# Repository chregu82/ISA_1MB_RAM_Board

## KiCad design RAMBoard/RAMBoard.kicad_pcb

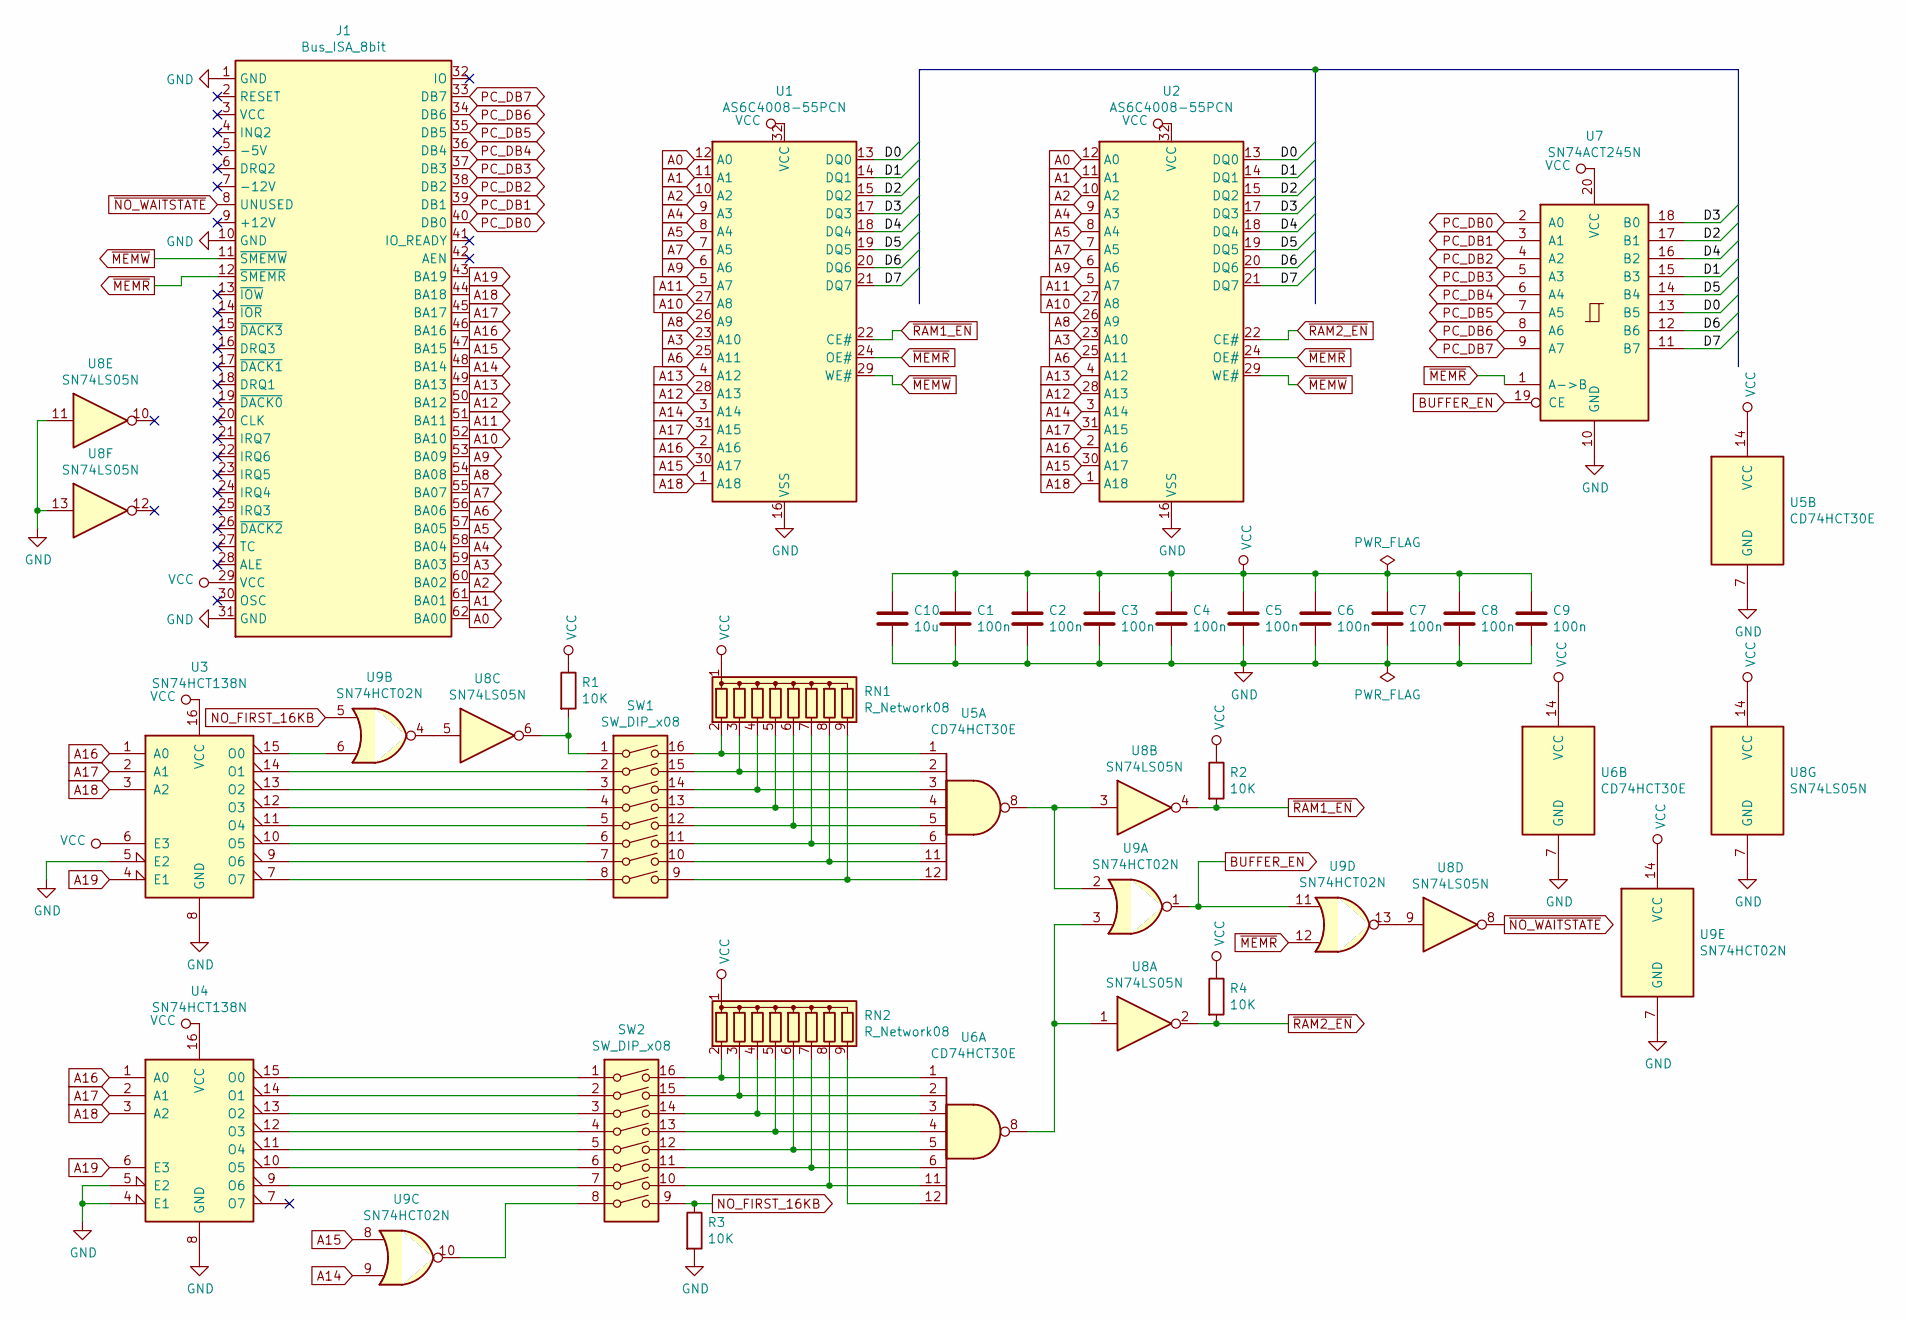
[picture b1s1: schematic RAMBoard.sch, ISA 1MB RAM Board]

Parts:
C1, C2, C3, C4, C5, C6, C7, C8, C9: 100n; C_Disc_D5.0mm_W2.5mm_P2.50mm
C10: 10u; C_Disc_D5.0mm_W2.5mm_P2.50mm
J1: Bus_ISA_8bit; BUS_XT
R1, R2, R3, R4: 10K; R_Axial_DIN0204_L3.6mm_D1.6mm_P5.08mm_Horizontal
RN1, RN2: R_Network08; R_Array_SIP9
SW1, SW2: SW_DIP_x08; SW_DIP_SPSTx08_Slide_9.78x22.5mm_W7.62mm_P2.54mm
U1, U2: AS6C4008-55PCN; DIP-32_W15.24mm
U3, U4: SN74HCT138N; DIP-16_W7.62mm
U5, U6: CD74HCT30E; DIP-14_W7.62mm
U7: SN74ACT245N; DIP-20_W7.62mm
U8: SN74LS05N; DIP-14_W7.62mm
U9: SN74HCT02N; DIP-14_W7.62mm

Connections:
/D0: U1.13 (DQ0), U2.13 (DQ0), U7.13 (B5)
/D1: U1.14 (DQ1), U2.14 (DQ1), U7.15 (B3)
/D2: U1.15 (DQ2), U2.15 (DQ2), U7.17 (B1)
/D3: U1.17 (DQ3), U2.17 (DQ3), U7.18 (B0)
/D4: U1.18 (DQ4), U2.18 (DQ4), U7.16 (B2)
/D5: U1.19 (DQ5), U2.19 (DQ5), U7.14 (B4)
/D6: U1.20 (DQ6), U2.20 (DQ6), U7.12 (B6)
/D7: U1.21 (DQ7), U2.21 (DQ7), U7.11 (B7)
A0: J1.62 (BA00), U1.12 (A0), U2.12 (A0)
A1: J1.61 (BA01), U1.11 (A1), U2.11 (A1)
A2: J1.60 (BA02), U1.10 (A2), U2.10 (A2)
A3: J1.59 (BA03), U1.23 (A10), U2.23 (A10)
A4: J1.58 (BA04), U1.9 (A3), U2.9 (A3)
A5: J1.57 (BA05), U1.8 (A4), U2.8 (A4)
A6: J1.56 (BA06), U1.25 (A11), U2.25 (A11)
A7: J1.55 (BA07), U1.7 (A5), U2.7 (A5)
A8: J1.54 (BA08), U1.26 (A9), U2.26 (A9)
A9: J1.53 (BA09), U1.6 (A6), U2.6 (A6)
A10: J1.52 (BA10), U1.27 (A8), U2.27 (A8)
A11: J1.51 (BA11), U1.5 (A7), U2.5 (A7)
A12: J1.50 (BA12), U1.28 (A13), U2.28 (A13)
A13: J1.49 (BA13), U1.4 (A12), U2.4 (A12)
A14: J1.48 (BA14), U1.3 (A14), U2.3 (A14), U9.9
A15: J1.47 (BA15), U1.30 (A17), U2.30 (A17), U9.8
A16: J1.46 (BA16), U1.2 (A16), U2.2 (A16), U3.1 (A0), U4.1 (A0)
A17: J1.45 (BA17), U1.31 (A15), U2.31 (A15), U3.2 (A1), U4.2 (A1)
A18: J1.44 (BA18), U1.1 (A18), U2.1 (A18), U3.3 (A2), U4.3 (A2)
A19: J1.43 (BA19), U3.4 (E1), U4.6 (E3)
BUFFER_EN: U7.19 (CE), U9.1, U9.11
GND: C1.2, C2.2, C3.2, C4.2, C5.2, C6.2, C7.2, C8.2, C9.2, C10.2, J1.1 (GND), J1.10 (GND), J1.31 (GND), R3.2, U1.16 (VSS), U2.16 (VSS), U3.5 (E2), U3.8 (GND), U4.4 (E1), U4.5 (E2), U4.8 (GND), U5.7 (GND), U6.7 (GND), U7.10 (GND), U8.7 (GND), U8.11, U8.13, U9.7 (GND); also elsewhere on the board
NO_FIRST_16KB: R3.1, SW2.9, U9.5
unnamed: R1.2, SW1.1, U8.6
unnamed: RN1.2 (R1), SW1.16, U5.1
unnamed: RN1.3 (R2), SW1.15, U5.2
unnamed: RN1.4 (R3), SW1.14, U5.3
unnamed: RN1.5 (R4), SW1.13, U5.4
unnamed: RN1.6 (R5), SW1.12, U5.5
unnamed: RN1.7 (R6), SW1.11, U5.6
unnamed: RN1.8 (R7), SW1.10, U5.11
unnamed: RN1.9 (R8), SW1.9, U5.12
unnamed: RN2.2 (R1), SW2.16, U6.1
unnamed: RN2.3 (R2), SW2.15, U6.2
unnamed: RN2.4 (R3), SW2.14, U6.3
unnamed: RN2.5 (R4), SW2.13, U6.4
unnamed: RN2.6 (R5), SW2.12, U6.5
unnamed: RN2.7 (R6), SW2.11, U6.6
unnamed: RN2.8 (R7), SW2.10, U6.11
unnamed: RN2.9 (R8), U6.12
unnamed: SW1.2, U3.14 (O1)
unnamed: SW1.3, U3.13 (O2)
unnamed: SW1.4, U3.12 (O3)
unnamed: SW1.5, U3.11 (O4)
unnamed: SW1.6, U3.10 (O5)
unnamed: SW1.7, U3.9 (O6)
unnamed: SW1.8, U3.7 (O7)
unnamed: SW2.1, U4.15 (O0)
unnamed: SW2.2, U4.14 (O1)
unnamed: SW2.3, U4.13 (O2)
unnamed: SW2.4, U4.12 (O3)
unnamed: SW2.5, U4.11 (O4)
unnamed: SW2.6, U4.10 (O5)
unnamed: SW2.7, U4.9 (O6)
unnamed: SW2.8, U9.10
unnamed: U3.15 (O0), U9.6
unnamed: U5.8, U8.3, U9.2
unnamed: U6.8, U8.1, U9.3
unnamed: U8.5, U9.4
unnamed: U8.9, U9.13
PC_DB0: J1.40 (DB0), U7.2 (A0)
PC_DB1: J1.39 (DB1), U7.3 (A1)
PC_DB2: J1.38 (DB2), U7.4 (A2)
PC_DB3: J1.37 (DB3), U7.5 (A3)
PC_DB4: J1.36 (DB4), U7.6 (A4)
PC_DB5: J1.35 (DB5), U7.7 (A5)
PC_DB6: J1.34 (DB6), U7.8 (A6)
PC_DB7: J1.33 (DB7), U7.9 (A7)
VCC: C1.1, C2.1, C3.1, C4.1, C5.1, C6.1, C7.1, C8.1, C9.1, C10.1, J1.29 (VCC), R1.1, R2.1, R4.1, RN1.1 (common), RN2.1 (common), U1.32 (VCC), U2.32 (VCC), U3.6 (E3), U3.16 (VCC), U4.16 (VCC), U5.14 (VCC), U6.14 (VCC), U7.20 (VCC), U8.14 (VCC), U9.14 (VCC)
~MEMR: J1.12 (~SMEMR), U1.24 (OE#), U2.24 (OE#), U7.1 (A->B), U9.12
~MEMW: J1.11 (~SMEMW), U1.29 (WE#), U2.29 (WE#)
~NO_WAITSTATE: J1.8 (UNUSED), U8.8
~RAM1_EN: R2.2, U1.22 (CE#), U8.4
~RAM2_EN: R4.2, U2.22 (CE#), U8.2

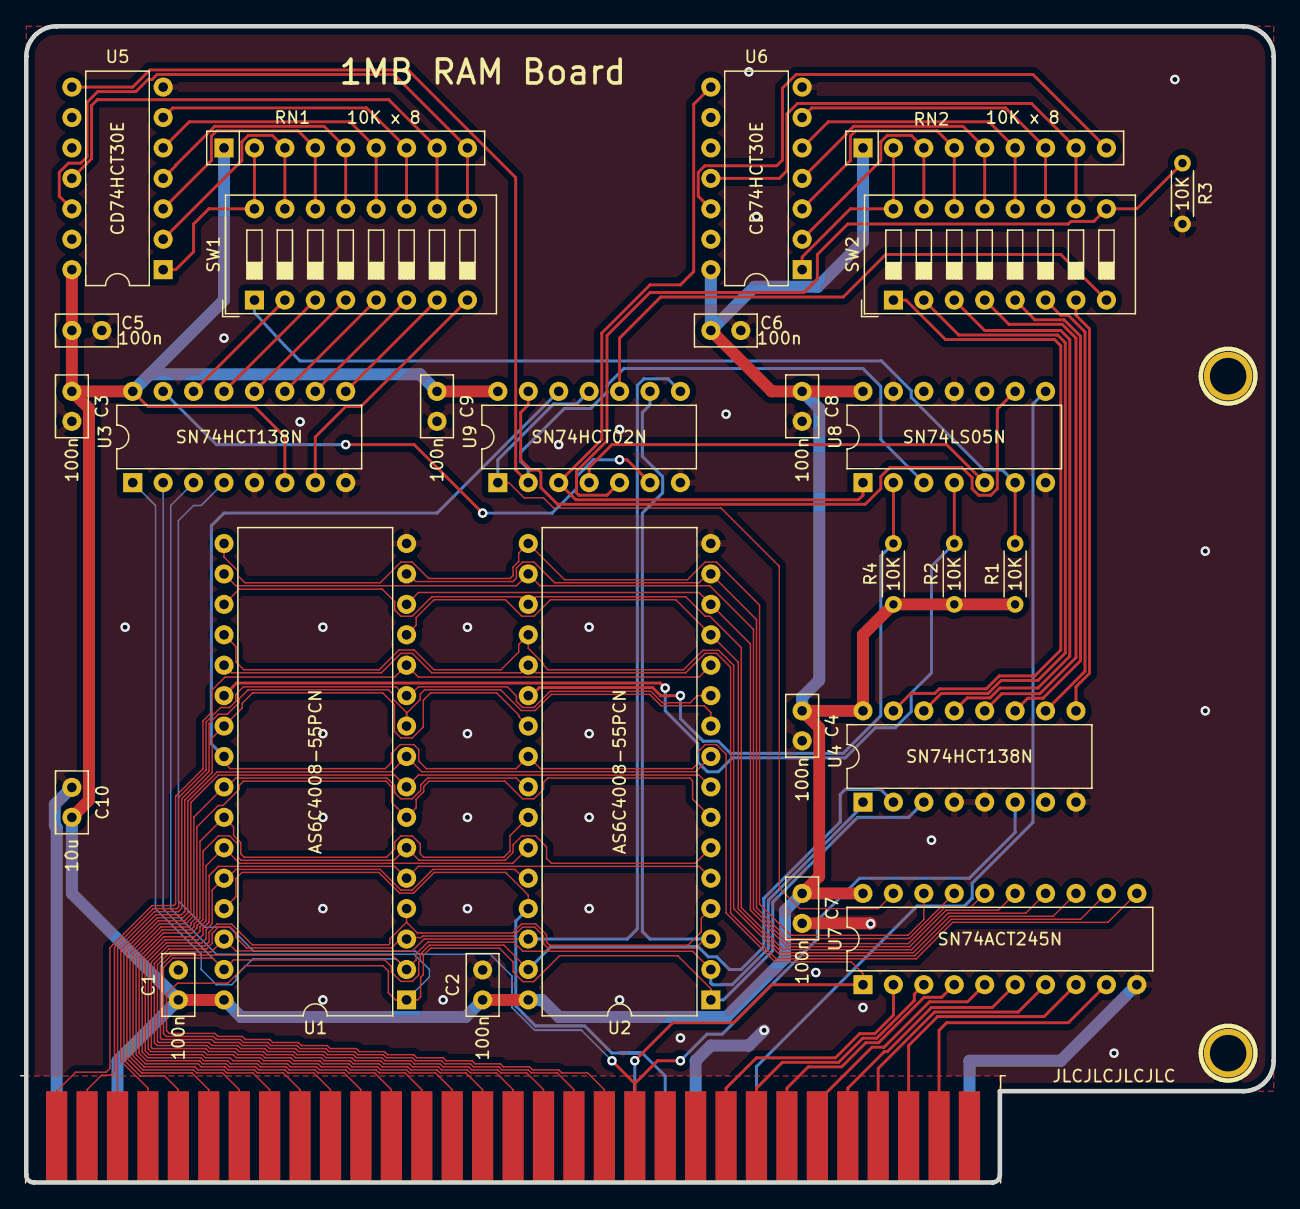
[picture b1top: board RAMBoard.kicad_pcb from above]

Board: 2 copper layers, 104.1 x 96.5 mm, 30 parts (0 on the bottom side), 82 nets.

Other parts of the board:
HOLE1, HOLE2: CONN_1; HOLE_3MM

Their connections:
GND: HOLE1.1, HOLE2.1; also elsewhere on the board

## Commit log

2021-03-10 Schematic and PCB
2021-03-10 PCB texts
